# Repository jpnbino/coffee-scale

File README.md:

# Coffee Scale Controller

Open-hardware electronics for a coffee scale controller. The project contains
the KiCad design, revision history, manufacturing records, release tooling, and
a browser-based review portal.

**Review portal:** <https://jpnbino.github.io/coffee-scale/> — schematic, PCB,
3D model, Gerbers and build files from the latest `main` build. It shows a
prototype design for review, not a production or supplier approval.

*Revision E routed prototype, shown as a faithful KiCad-derived isometric render.
The image is for design review; the hardware is not yet production-approved.*

## Current status

- **Hardware:** Revision E routed prototype.
- **Firmware:** prototype MicroPython firmware, tested on a breadboard build, is in
  [coffee-scale-firmware](https://github.com/jpnbino/coffee-scale-firmware);
  it is not yet ported to this PCB.
- **Not complete:** Firmware for Rev E, physical validation, supplier approval, and final
  assembly decisions.
- **Authoritative design:** `src/`.
- **Historical records:** `src/fabrication/` and revision snapshots under `src/`.

This repository is public and intended for open-hardware development. A
maintainer still needs to choose and add the project's hardware, software, and
documentation licenses; no legal license was guessed.

## Repository map

| Path | Purpose |
| --- | --- |
| `src/` | KiCad sources, local libraries, models, revision snapshots, and historical fabrication data |
| `assembly/` | Assembly profile used by the release workflow |
| `scripts/legacy/` | Historical placement, routing, revision, and packaging utilities |
| `tools/` | Maintained release and portal build tooling |
| `docs/` | Detailed board, manufacturing, and compatibility documentation |
| `tests/` | Release and viewer regression checks |
| `web/` | Browser review portal source and pinned vendor assets |
| `build/`, `tmp/`, `work/`, `outputs/` | Generated or intermediate files; not committed |

## Quick start

Requirements (Windows, macOS or Linux):

- KiCad 10, which provides `kicad-cli`
- Node.js 22 or newer — no `npm install` needed; the tooling has no dependencies

From the repository root:

```sh
node release.mjs --validate-only   # ERC, DRC, schematic parity and dimensions
node release.mjs                   # full prototype release build
node preview.mjs                   # view it at http://127.0.0.1:8787 (see Review portal)
```

The same commands are available as `npm run validate`, `npm run release` and
`npm run preview`. `node release.mjs --require-assembly-ready` additionally
fails the build while assembly blockers remain.

`kicad-cli` is found from `--kicad-cli <path>`, then the `KICAD_CLI`
environment variable, then `PATH`, then the standard install location
(`C:/Program Files/KiCad/10.0/bin` on Windows,
`/Applications/KiCad/KiCad.app/Contents/MacOS` on macOS, `/usr/bin` on Linux).
Each build creates a new timestamped folder under `build/releases/`.

## Review portal

Every release build includes a browser-based review portal (`site/`):

| Page | What it shows |
| --- | --- |
| Overview | Board summary, status and key facts |
| Explore board | Top/bottom copper, schematic and 3D model with part search |
| Board statistics, Layer stackup | Counts and drill table; order parameters checked against KiCad, cross-section, track current estimates |
| Gerber inspection | The exact manufacturing files, with layer presets, measurement and checks before ordering (placement, paste, pin maps) |
| Build & manufacture, Enclosure & mechanics | Fabrication, assembly-draft and mechanical downloads |
| Versions & changes | Rev D, archived Rev E and the current build compared |
| Documentation | The notes in `docs/board/` |

### Online

<https://jpnbino.github.io/coffee-scale/> is republished automatically after
every push to `main`, once the tests and the full KiCad build have passed.
Pull requests are built and checked but never published.

### Locally

After a build, serve it with:

```sh
node release.mjs     # build first (a few minutes); needs KiCad
node preview.mjs     # then open http://127.0.0.1:8787
```

- `preview.mjs` serves the newest *complete* build in `build/releases/`.
  Stop it with Ctrl+C.
- Use `--port 8080` if 8787 is taken, or `--site <build>/site` to serve a
  specific build.
- The server only listens on your own machine (`127.0.0.1`); nothing is
  published.
- Don't open `index.html` by double-clicking it: browsers block the 3D model and
  interactive drawings on `file://` pages.
- After pulling changes to `web/` or `tools/`, run `node release.mjs` again.
  Existing builds keep the portal code they were built with.

### From a CI build

Each GitHub Actions run keeps its full build for 14 days. Open the run under
**Actions**, download **release-build** from *Artifacts*, unzip it, then:

```sh
node preview.mjs --site ~/Downloads/release-build/<build-id>/site
```

## Release contents

Each successful build contains:

- `source/` — isolated KiCad design snapshot
- `reports/` — ERC, DRC, netlist, statistics, and build log
- `fabrication/` — Gerbers, drills, and manufacturing notes
- `assembly/` — BOM, placement data, IPC-2581, stencil layers, and readiness
- `mechanical/` — STEP/DXF exports and interface data
- `site/` — review portal and downloadable packages
- `manifest.json` — hashes, tool versions, status, and readiness

The assembly profile in `assembly/profile.csv` is intentionally retained: the
release workflow reads it to apply population stages, sourcing metadata,
rotation corrections, and verification state. It is not proof of supplier
approval.

## Checks

```sh
npm test        # or: node --test tests/*.test.mjs
```

GitHub Actions runs these tests on Windows, macOS and Linux, then runs the
validation and a full release build inside the official, version-pinned
`kicad/kicad` container. The build is attached to each run as an artifact.

See `docs/board/` for the detailed circuit, assembly, mechanical and
manufacturing notes, and `docs/maintainer/` for how the portal's viewers work. Legacy utilities should be run from the repository root;
they write candidates and intermediate files to their existing revision and
`tmp/` locations.

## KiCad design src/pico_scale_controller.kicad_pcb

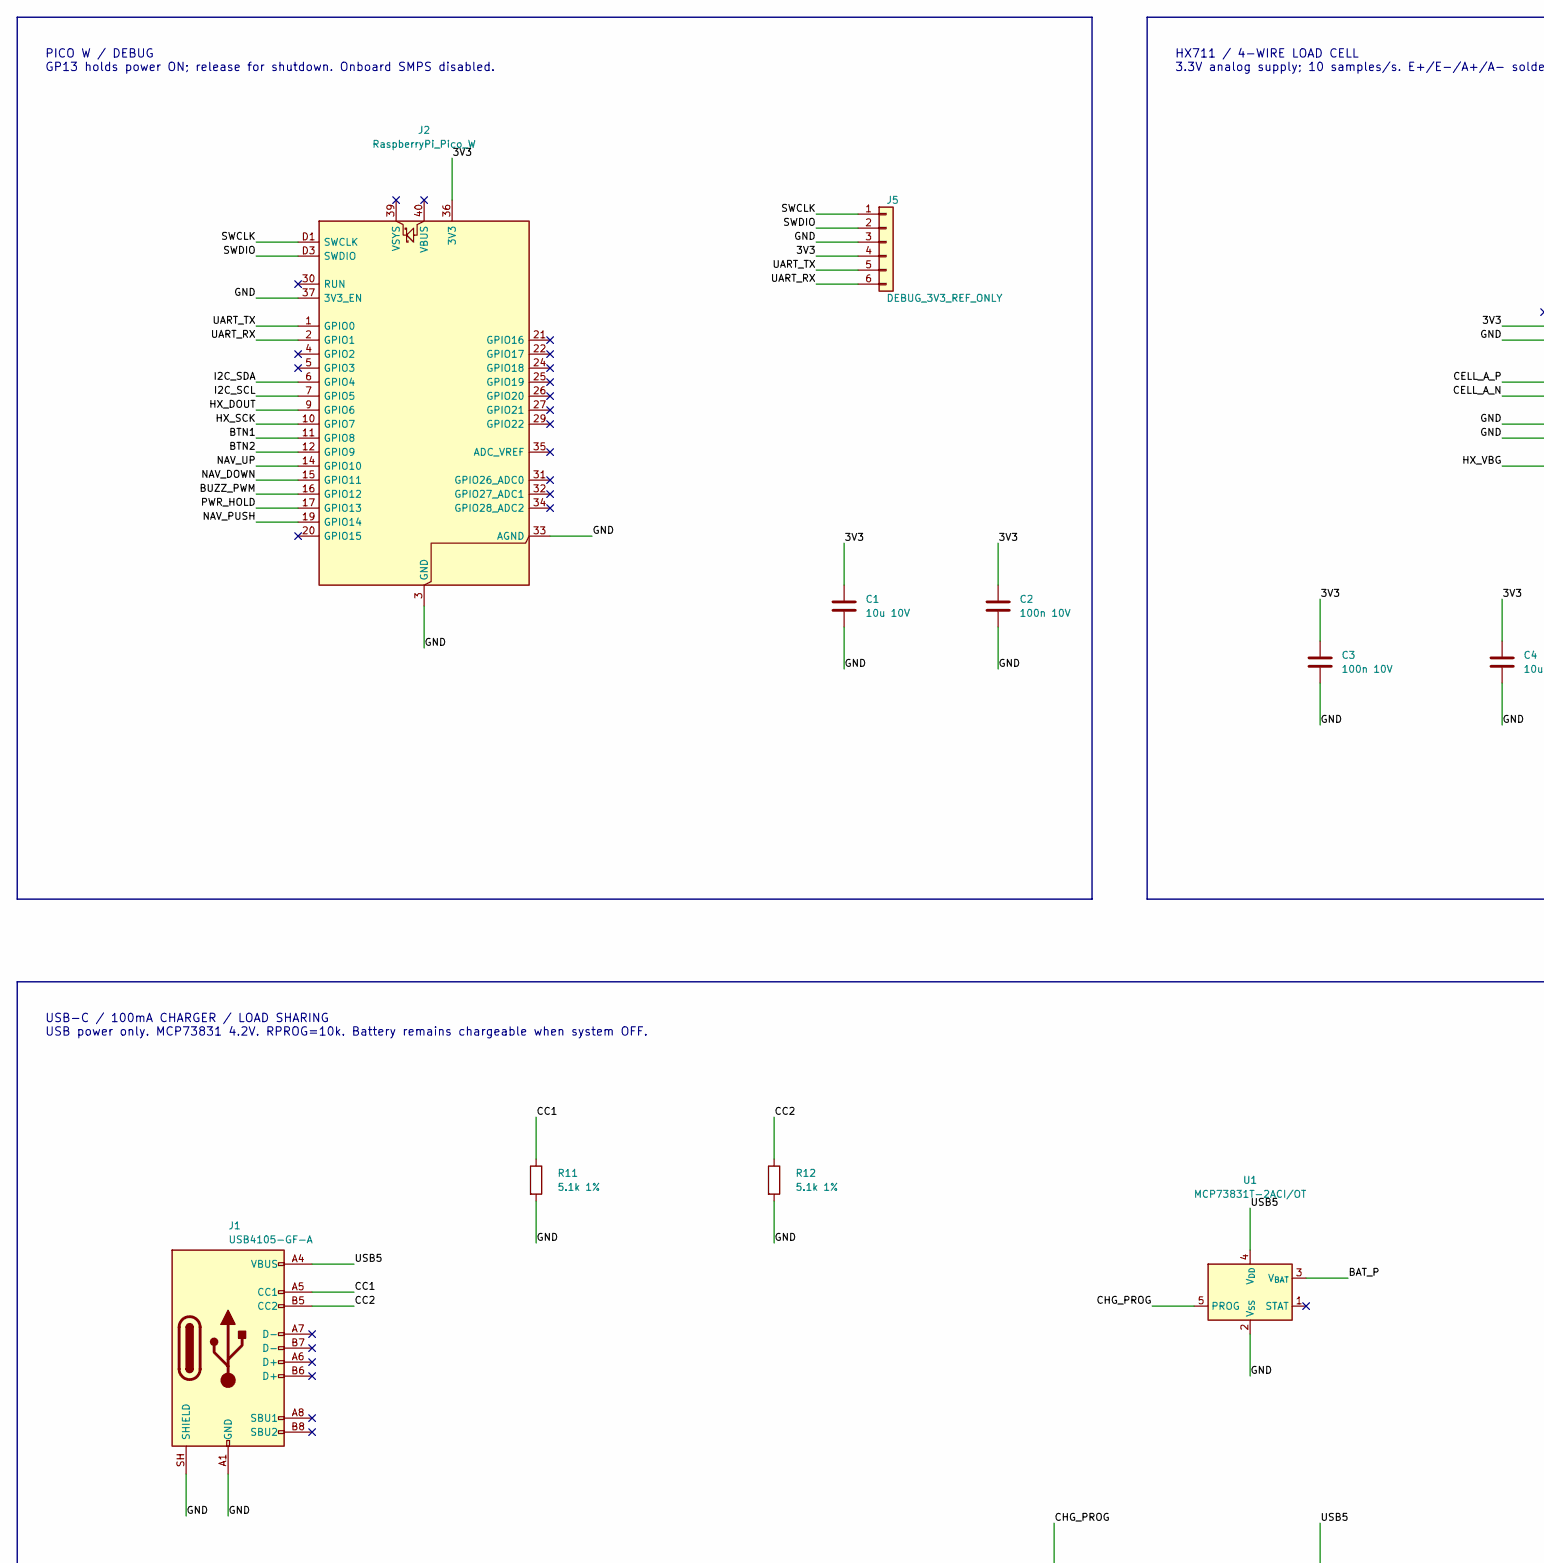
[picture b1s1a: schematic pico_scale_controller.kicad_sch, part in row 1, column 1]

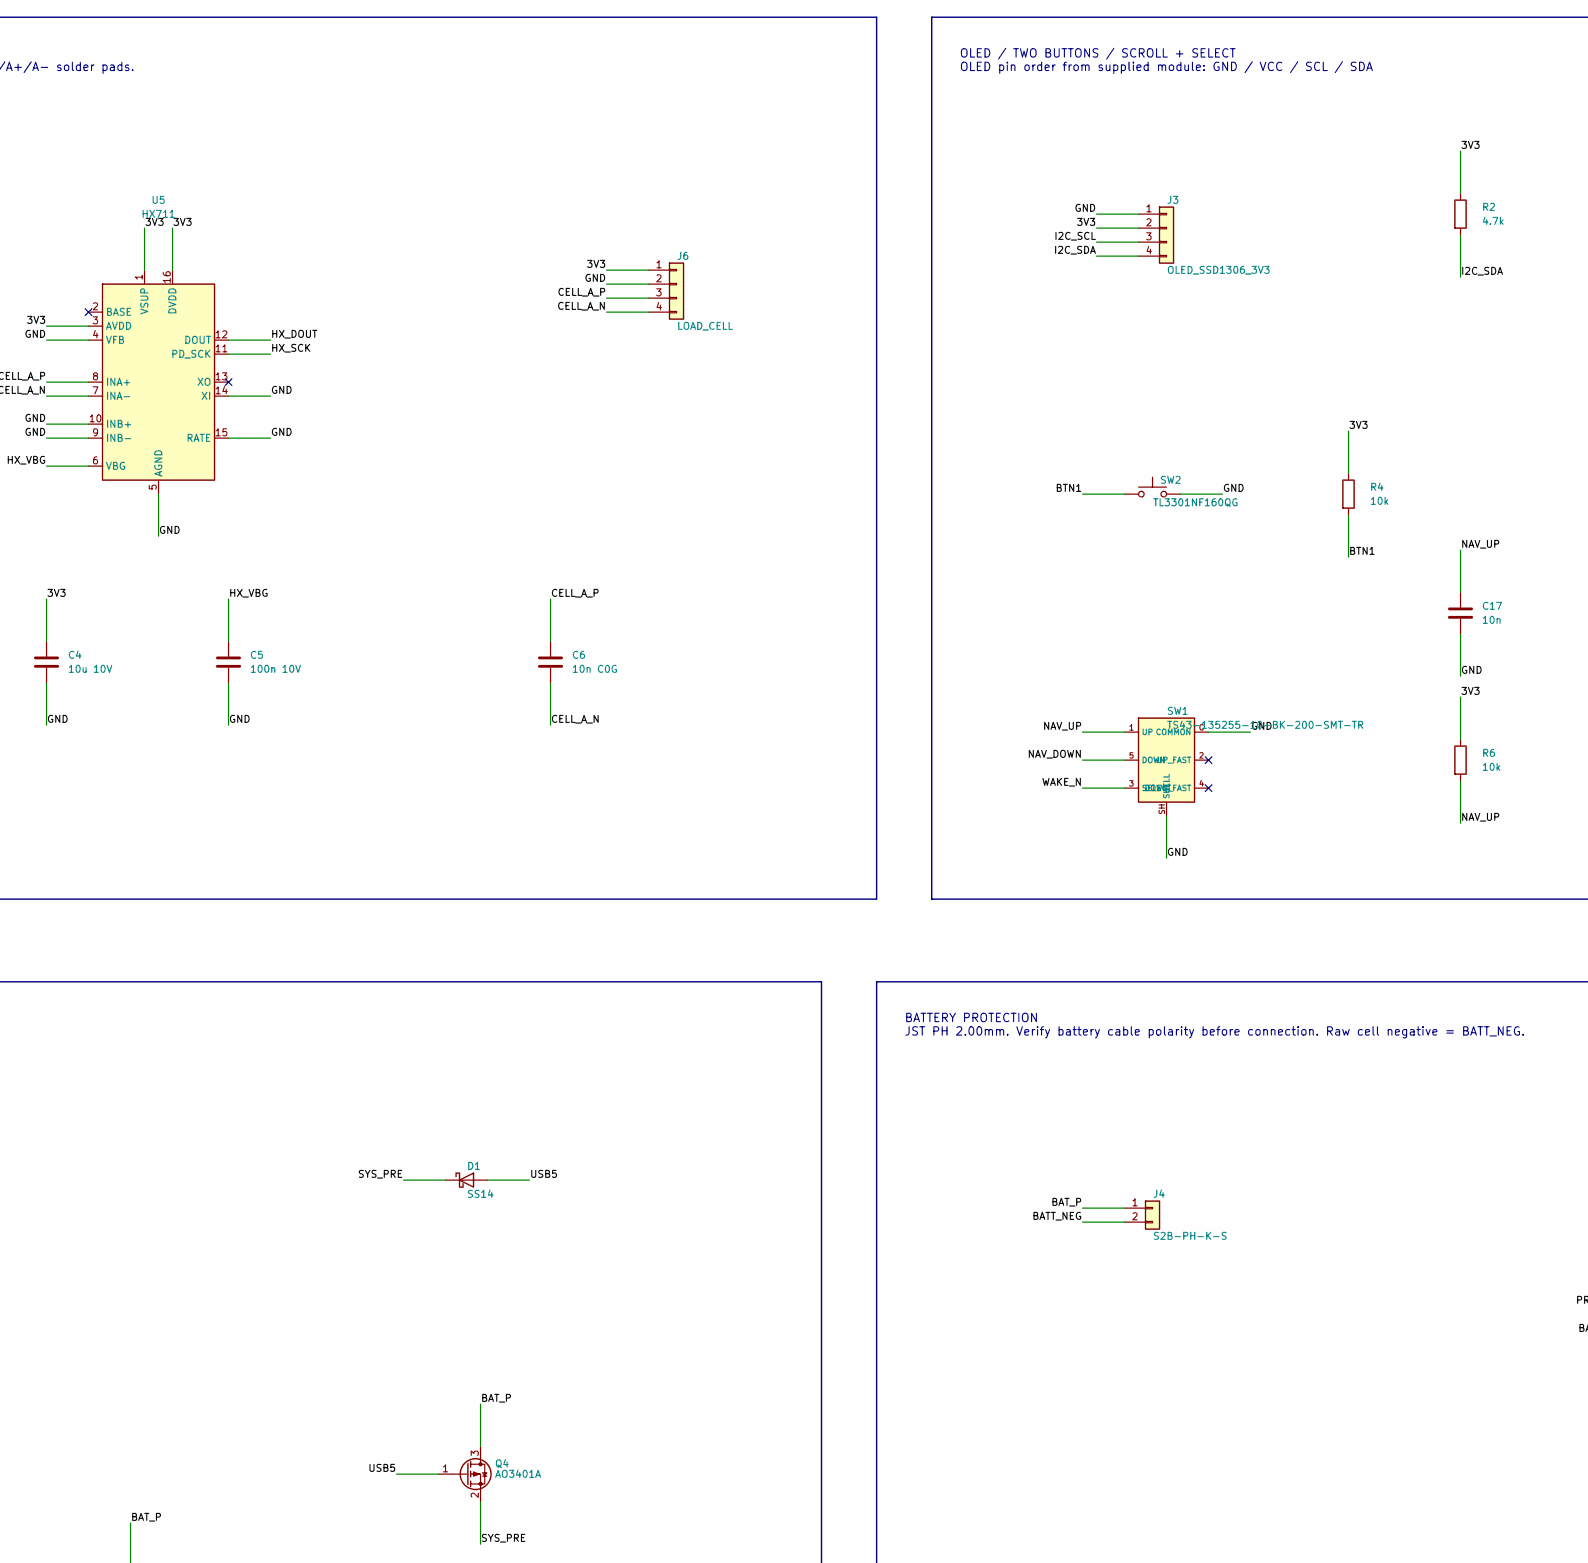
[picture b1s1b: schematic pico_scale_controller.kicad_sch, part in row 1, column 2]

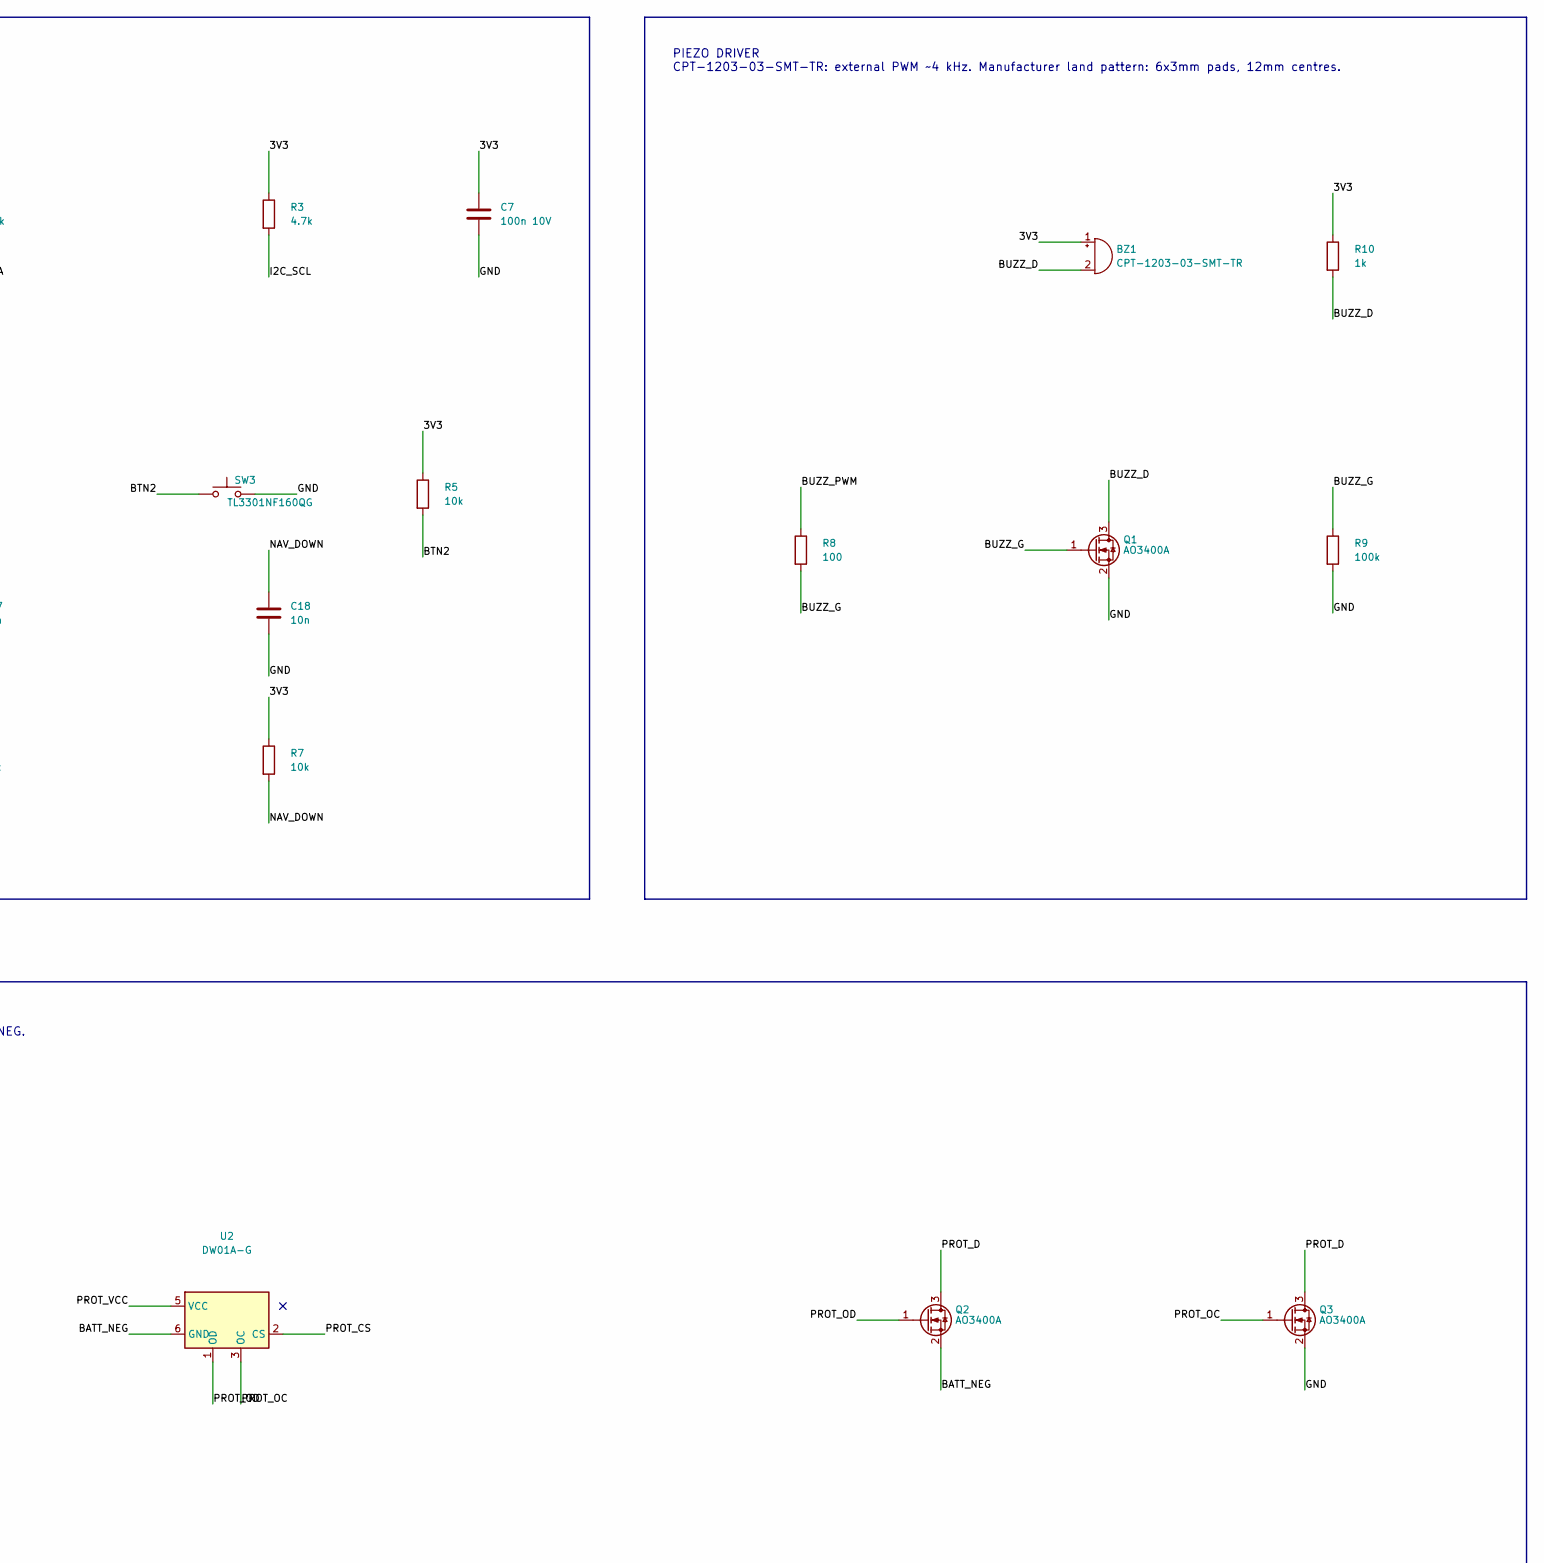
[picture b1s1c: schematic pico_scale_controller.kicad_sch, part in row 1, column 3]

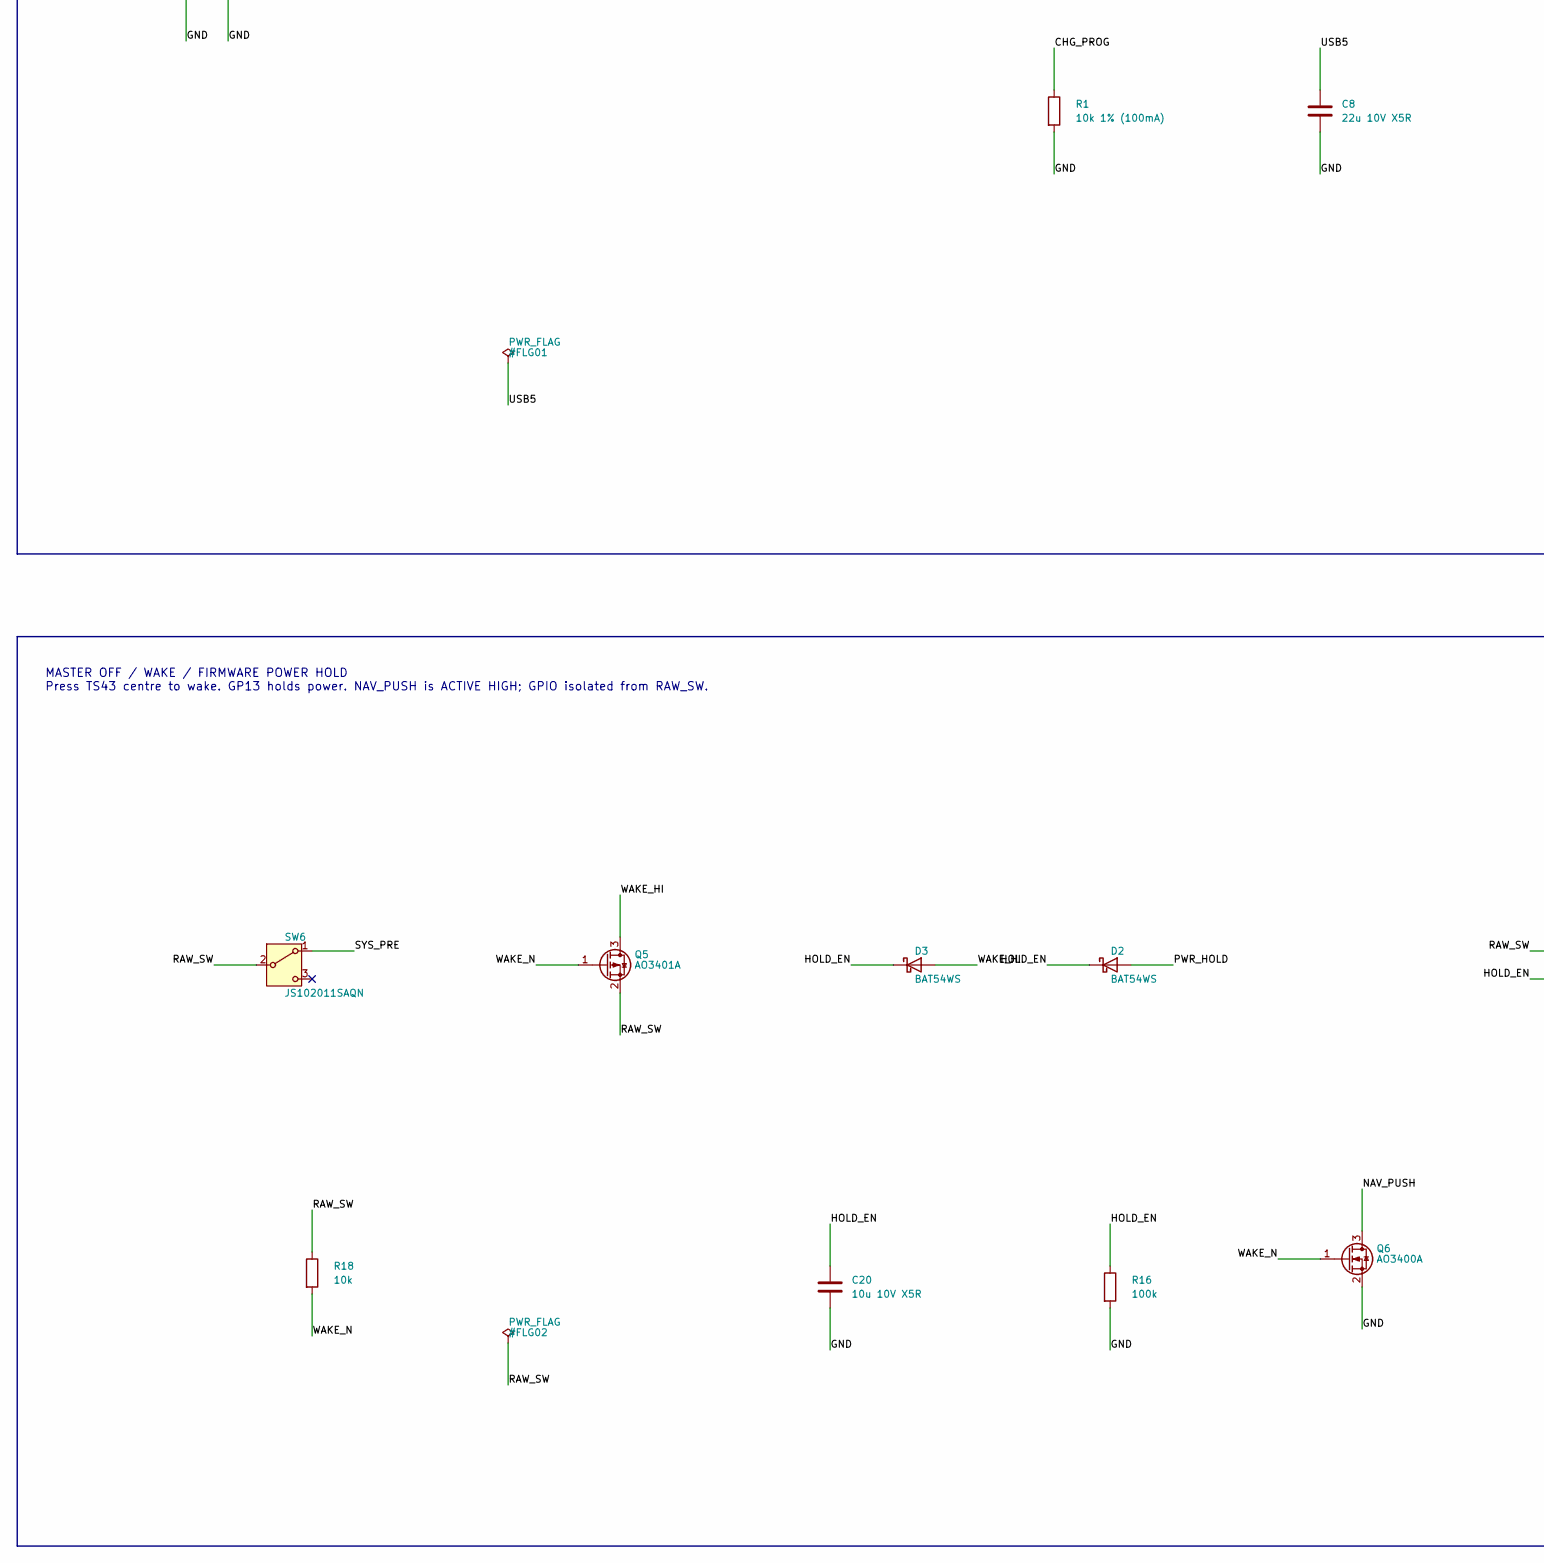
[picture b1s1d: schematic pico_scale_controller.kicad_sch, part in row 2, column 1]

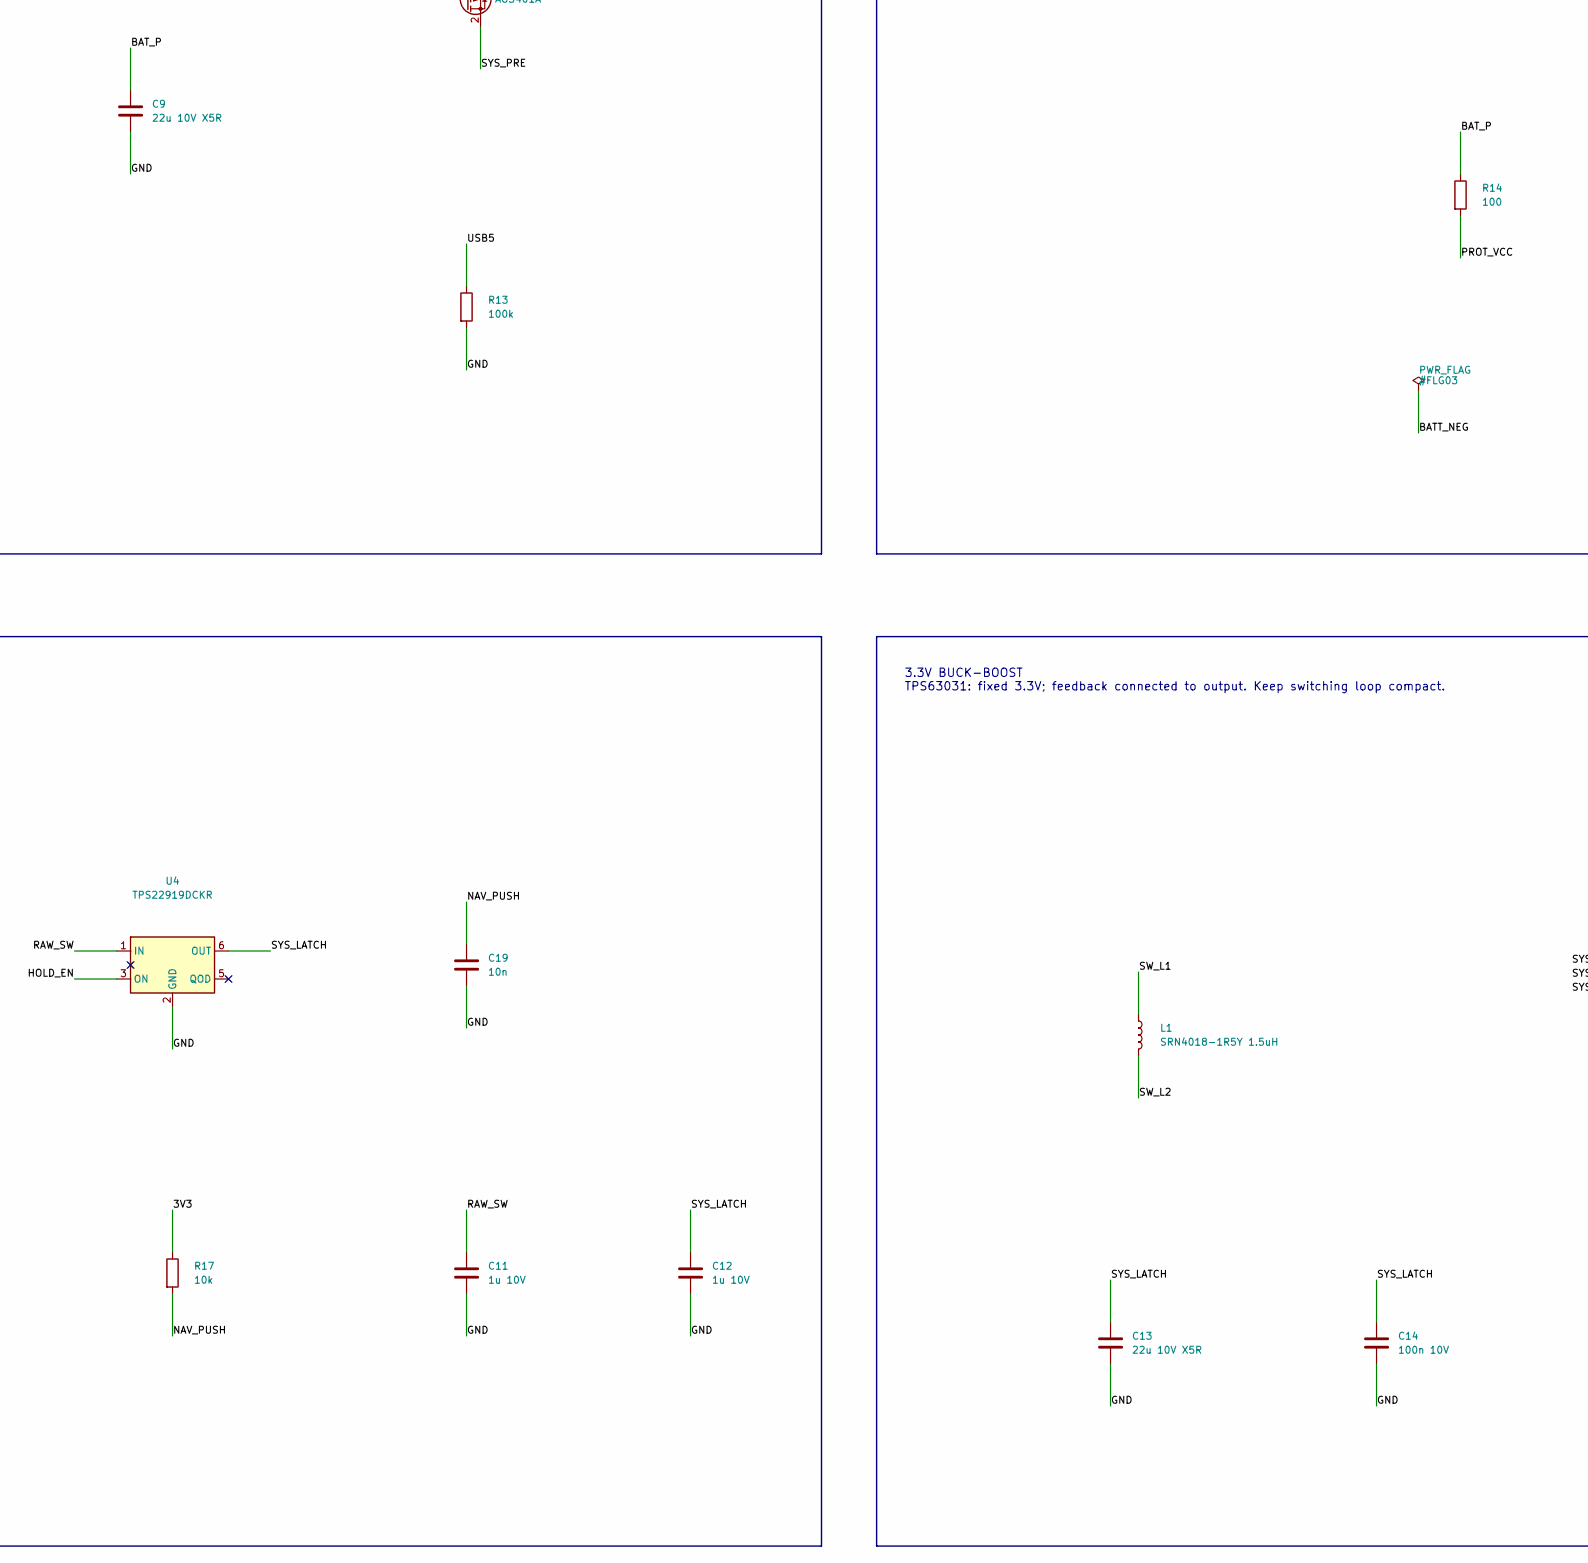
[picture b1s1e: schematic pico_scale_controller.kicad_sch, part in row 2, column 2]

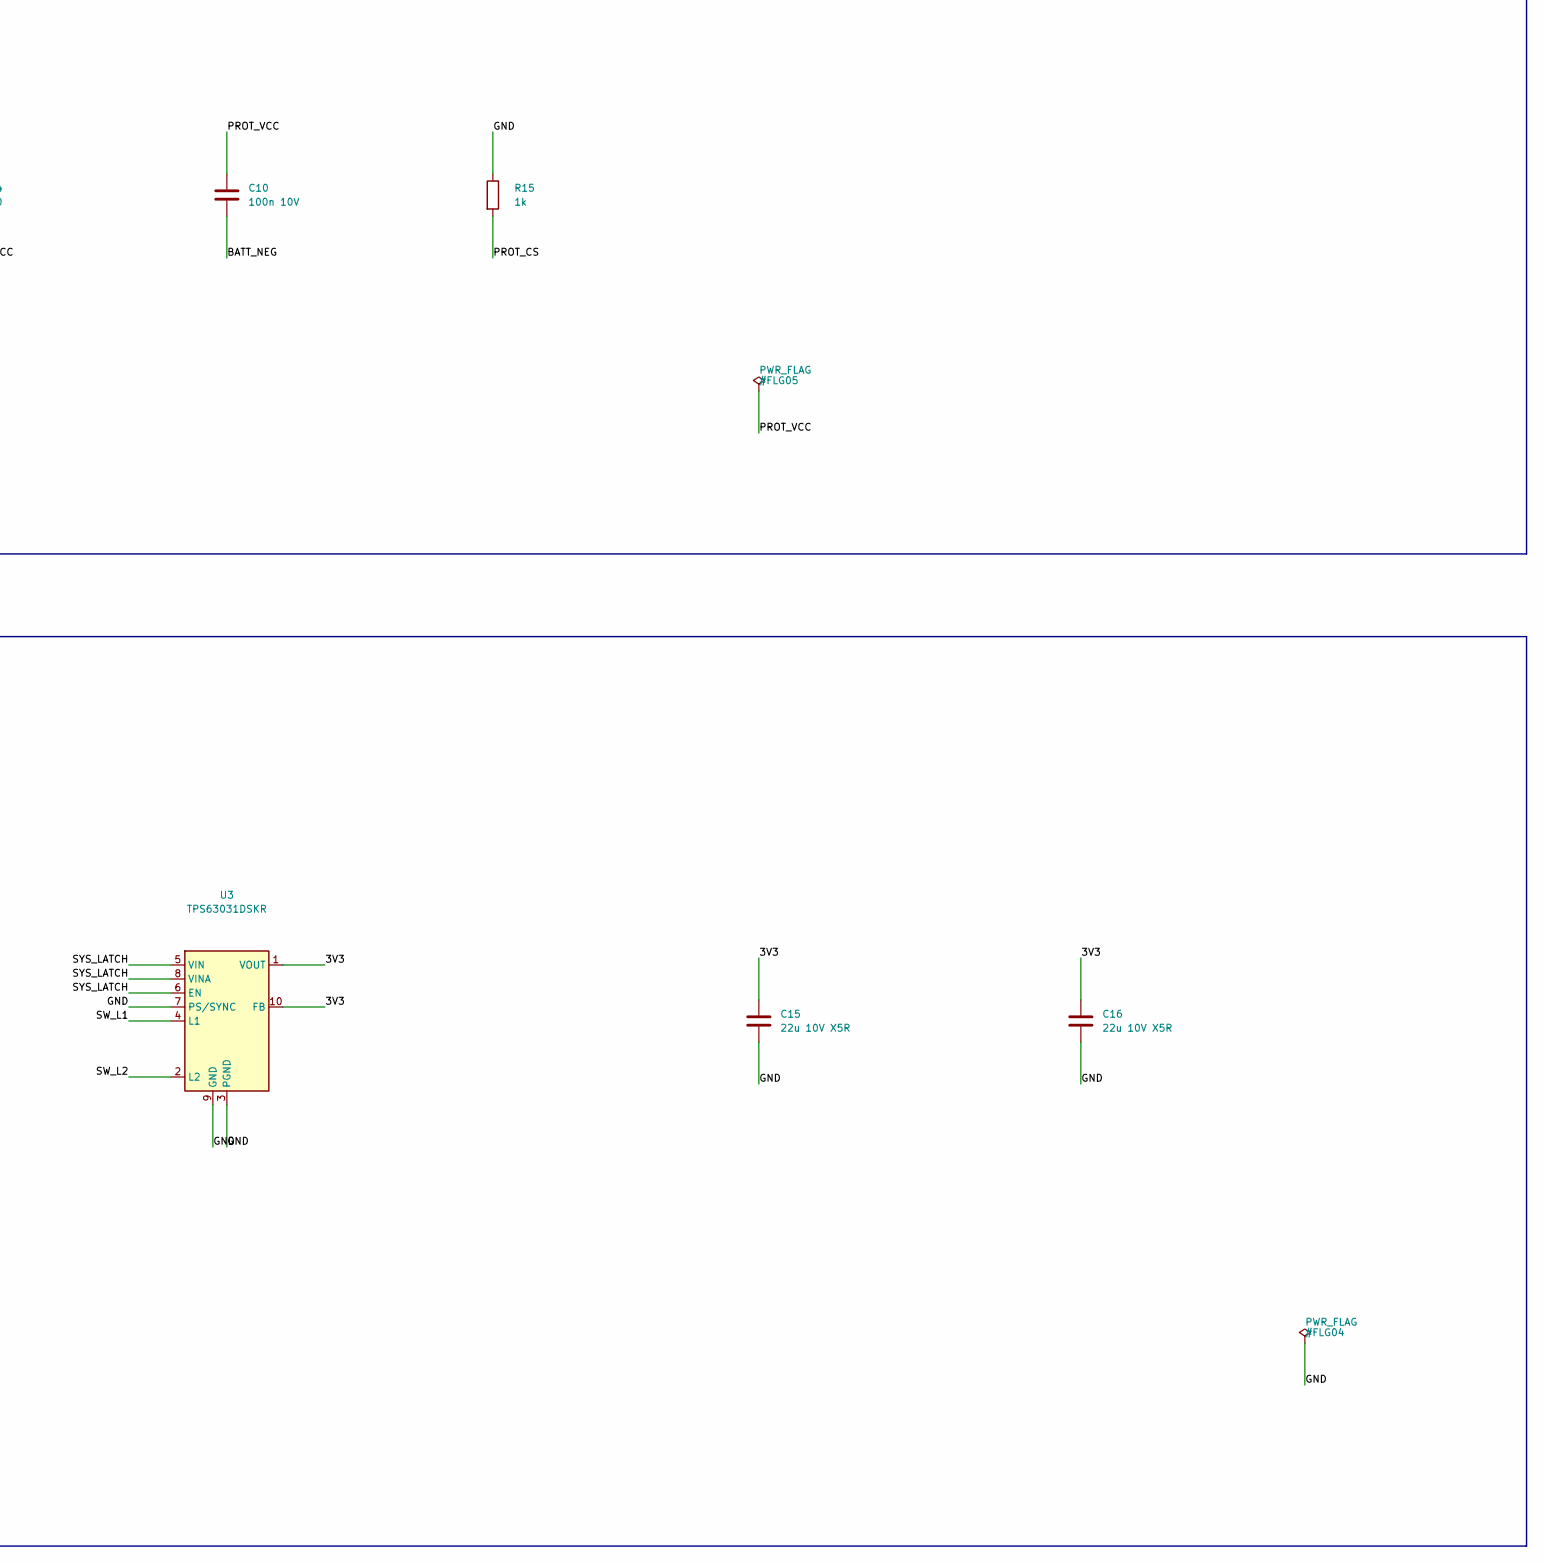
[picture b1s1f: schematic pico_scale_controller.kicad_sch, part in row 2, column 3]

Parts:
BZ1: CPT-1203-03-SMT-TR
C1, C4: 10u 10V; C_0603_1608Metric
C2, C3, C5, C7, C10, C14: 100n 10V; C_0603_1608Metric
C6: 10n C0G; C_0603_1608Metric
C8, C9, C13, C15, C16: 22u 10V X5R; C_0805_2012Metric
C11, C12: 1u 10V; C_0603_1608Metric
C17, C18, C19: 10n; C_0603_1608Metric
C20: 10u 10V X5R; C_0805_2012Metric
D1: SS14; D_SMA
D2, D3: BAT54WS; D_SOD-323
J1: USB4105-GF-A; USB4105_GND_Rounded
J2: RaspberryPi_Pico_W; Pico_W_Hybrid
J3: OLED_SSD1306_3V3; PinHeader_1x04_P2.54mm_Vertical
J4: S2B-PH-K-S; JST_PH_S2B-PH-K_1x02_P2.00mm_Horizontal
J5: DEBUG_3V3_REF_ONLY; PinHeader_1x06_P2.54mm_Vertical
J6: LOAD_CELL; LoadCell_4Pads
L1: SRN4018-1R5Y 1.5uH; L_Bourns-SRN4018
Q1, Q2, Q3, Q6: AO3400A; SOT-23
Q4, Q5: AO3401A; SOT-23
R1: 10k 1% (100mA); R_0603_1608Metric
R2, R3: 4.7k; R_0603_1608Metric
R4, R5, R6, R7, R17, R18: 10k; R_0603_1608Metric
R8, R14: 100; R_0603_1608Metric
R9, R13, R16: 100k; R_0603_1608Metric
R10, R15: 1k; R_0603_1608Metric
R11, R12: 5.1k 1%; R_0603_1608Metric
SW1: TS43-135255-10-BK-200-SMT-TR; TS43_135255
SW2, SW3: TL3301NF160QG; SW_Push_1P1T_NO_E-Switch_TL3301NxxxxxG
SW6: JS102011SAQN; SW_SPDT_CK_JS102011SAQN
U1: MCP73831T-2ACI/OT; SOT-23-5
U2: DW01A-G; SOT-23-6
U3: TPS63031DSKR; WSON-10-1EP_2.5x2.5mm_P0.5mm_EP1.2x2mm
U4: TPS22919DCKR; SOT-363_SC-70-6
U5: HX711; SOIC-16_3.9x9.9mm_P1.27mm

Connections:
/3V3: BZ1.1 (+), C1.1, C2.1, C3.1, C4.1, C7.1, C15.1, C16.1, J2.36 (3V3), J3.2, J5.4, J6.1, R2.1, R3.1, R4.1, R5.1, R6.1, R7.1, R10.1, R17.1, U3.1 (VOUT), U3.10 (FB), U5.1 (VSUP), U5.3 (AVDD), U5.16 (DVDD)
/BATT_NEG: C10.2, J4.2, Q2.2 (S), U2.6 (GND)
/BAT_P: C9.1, J4.1, Q4.3 (D), R14.1, U1.3 (V_{BAT})
/BTN1: J2.11 (GPIO8), R4.2, SW2.1
/BTN2: J2.12 (GPIO9), R5.2, SW3.1
/BUZZ_D: BZ1.2 (-), Q1.3 (D), R10.2
/BUZZ_G: Q1.1 (G), R8.2, R9.1
/BUZZ_PWM: J2.16 (GPIO12), R8.1
/CC1: J1.A5 (CC1), R11.1
/CC2: J1.B5 (CC2), R12.1
/CELL_A_N: C6.2, J6.4, U5.7 (INA-)
/CELL_A_P: C6.1, J6.3, U5.8 (INA+)
/CHG_PROG: R1.1, U1.5 (PROG)
/GND: C1.2, C2.2, C3.2, C4.2, C5.2, C7.2, C8.2, C9.2, C11.2, C12.2, C13.2, C14.2, C15.2, C16.2, C17.2, C18.2, C19.2, C20.2, J1.A1 (GND), J1.A12 (GND), J1.B1 (GND), J1.B12 (GND), J1.SH (SHIELD), J2.3 (GND), J2.8 (GND), J2.13 (GND), J2.18 (GND), J2.23 (GND), J2.28 (GND), J2.33 (AGND), J2.37 (3V3_EN), J2.38 (GND), J2.D2 (GND), J3.1, J5.3, J6.2, Q1.2 (S), Q3.2 (S), Q6.2 (S), R1.2, R9.2, R11.2, R12.2, R13.2, R15.1, R16.2, SW1.C (COMMON), SW1.SH (SHELL), SW2.2, SW3.2, U1.2 (V_{SS}), U3.3 (PGND), U3.7 (PS/SYNC), U3.9 (GND), U3.11 (PGND), U4.2 (GND), U5.4 (VFB), U5.5 (AGND), U5.9 (INB-), U5.10 (INB+), U5.14 (XI), U5.15 (RATE)
/HOLD_EN: C20.1, D2.1 (K), D3.1 (K), R16.1, U4.3 (ON)
/HX_DOUT: J2.9 (GPIO6), U5.12 (DOUT)
/HX_SCK: J2.10 (GPIO7), U5.11 (PD_SCK)
/HX_VBG: C5.1, U5.6 (VBG)
/I2C_SCL: J2.7 (GPIO5), J3.3, R3.2
/I2C_SDA: J2.6 (GPIO4), J3.4, R2.2
/NAV_DOWN: C18.1, J2.15 (GPIO11), R7.2, SW1.5 (DOWN)
/NAV_PUSH: C19.1, J2.19 (GPIO14), Q6.3 (D), R17.2
/NAV_UP: C17.1, J2.14 (GPIO10), R6.2, SW1.1 (UP)
/PROT_CS: R15.2, U2.2 (CS)
/PROT_D: Q2.3 (D), Q3.3 (D)
/PROT_OC: Q3.1 (G), U2.3 (OC)
/PROT_OD: Q2.1 (G), U2.1 (OD)
/PROT_VCC: C10.1, R14.2, U2.5 (VCC)
/PWR_HOLD: D2.2 (A), J2.17 (GPIO13)
/RAW_SW: C11.1, Q5.2 (S), R18.1, SW6.2 (B), U4.1 (IN)
/SWCLK: J2.D1 (SWCLK), J5.1
/SWDIO: J2.D3 (SWDIO), J5.2
/SW_L1: L1.1, U3.4 (L1)
/SW_L2: L1.2, U3.2 (L2)
/SYS_LATCH: C12.1, C13.1, C14.1, U3.5 (VIN), U3.6 (EN), U3.8 (VINA), U4.6 (OUT)
/SYS_PRE: D1.1 (K), Q4.2 (S), SW6.1 (A)
/UART_RX: J2.2 (GPIO1), J5.6
/UART_TX: J2.1 (GPIO0), J5.5
/USB5: C8.1, D1.2 (A), J1.A4 (VBUS), J1.A9 (VBUS), J1.B4 (VBUS), J1.B9 (VBUS), Q4.1 (G), R13.1, U1.4 (V_{DD})
/WAKE_HI: D3.2 (A), Q5.3 (D)
/WAKE_N: Q5.1 (G), Q6.1 (G), R18.2, SW1.3 (SELECT)

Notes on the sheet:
PICO W / DEBUG GP13 holds power ON; release for shutdown. Onboard SMPS disabled.
HX711 / 4-WIRE LOAD CELL 3.3V analog supply; 10 samples/s. E+/E-/A+/A- solder pads.
OLED / TWO BUTTONS / SCROLL + SELECT OLED pin order from supplied module: GND / VCC / SCL / SDA
PIEZO DRIVER CPT-1203-03-SMT-TR: external PWM ~4 kHz. Manufacturer land pattern: 6x3mm pads, 12mm centres.
USB-C / 100mA CHARGER / LOAD SHARING USB power only. MCP73831 4.2V. RPROG=10k. Battery remains chargeable when system OFF.
BATTERY PROTECTION JST PH 2.00mm. Verify battery cable polarity before connection. Raw cell negative = BATT_NEG.
MASTER OFF / WAKE / FIRMWARE POWER HOLD Press TS43 centre to wake. GP13 holds power. NAV_PUSH is ACTIVE HIGH; GPIO isolated from RAW_SW.
3.3V BUCK-BOOST TPS63031: fixed 3.3V; feedback connected to output. Keep switching loop compact.

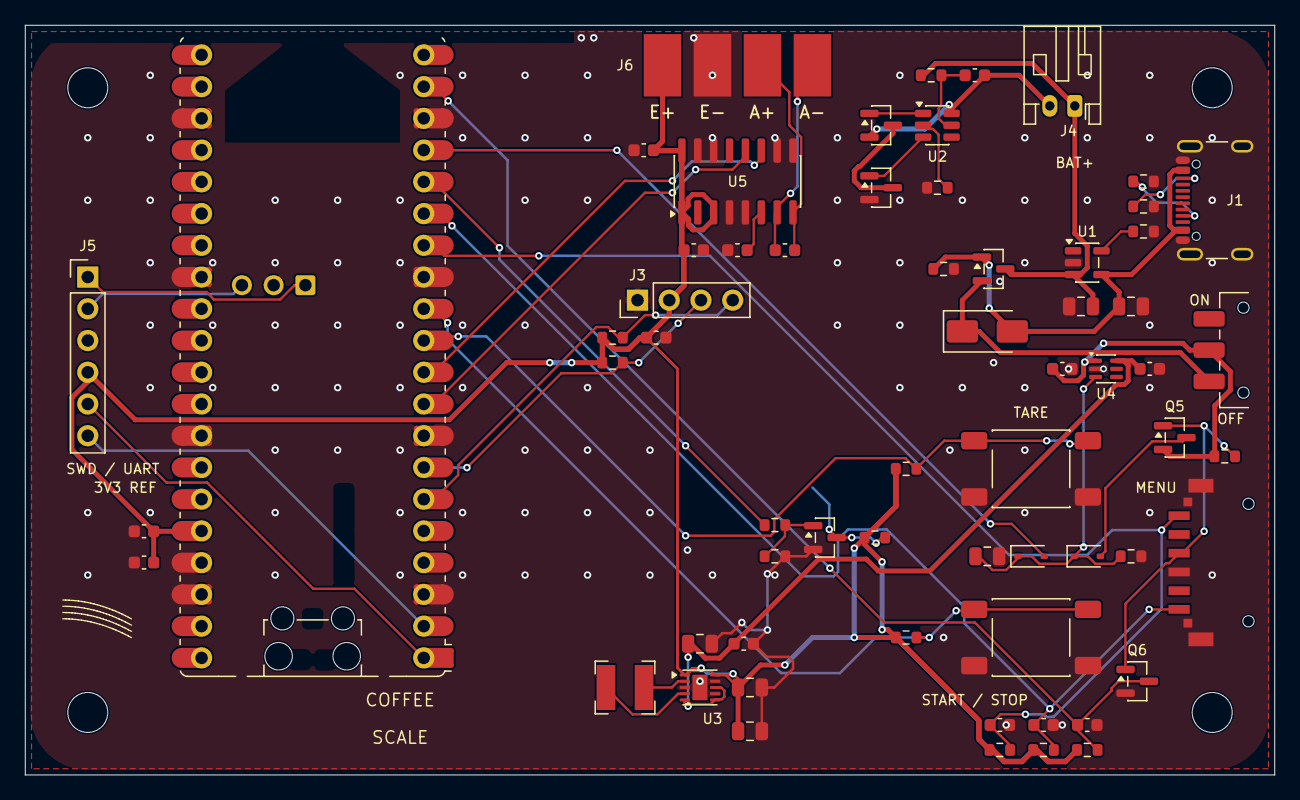
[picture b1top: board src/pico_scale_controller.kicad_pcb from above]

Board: 2 copper layers, 100.0 x 60.0 mm, 68 parts (1 on the bottom side), 41 nets.

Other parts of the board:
H1, H2, H3, H4: MountingHole_3.2mm_M3

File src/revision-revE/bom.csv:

Reference,Value / part,Footprint,Side
BZ1,CPT-1203-03-SMT-TR,CPT-1203-03-SMT-TR,bottom
C1,10u 10V,C_0603_1608Metric,top
C10,100n 10V,C_0603_1608Metric,top
C11,1u 10V,C_0603_1608Metric,top
C12,1u 10V,C_0603_1608Metric,top
C13,22u 10V X5R,C_0805_2012Metric,top
C14,100n 10V,C_0603_1608Metric,top
C15,22u 10V X5R,C_0805_2012Metric,top
C16,22u 10V X5R,C_0805_2012Metric,top
C17,10n,C_0603_1608Metric,top
C18,10n,C_0603_1608Metric,top
C19,10n,C_0603_1608Metric,top
C2,100n 10V,C_0603_1608Metric,top
C20,10u 10V X5R,C_0805_2012Metric,top
C3,100n 10V,C_0603_1608Metric,top
C4,10u 10V,C_0603_1608Metric,top
C5,100n 10V,C_0603_1608Metric,top
C6,10n C0G,C_0603_1608Metric,top
C7,100n 10V,C_0603_1608Metric,top
C8,22u 10V X5R,C_0805_2012Metric,top
C9,22u 10V X5R,C_0805_2012Metric,top
D1,SS14,D_SMA,top
D2,BAT54WS,D_SOD-323,top
D3,BAT54WS,D_SOD-323,top
H1,MountingHole_3.2mm_M3,MountingHole_3.2mm_M3,top
H2,MountingHole_3.2mm_M3,MountingHole_3.2mm_M3,top
H3,MountingHole_3.2mm_M3,MountingHole_3.2mm_M3,top
H4,MountingHole_3.2mm_M3,MountingHole_3.2mm_M3,top
J1,USB4105-GF-A,USB4105_GND_Rounded,top
J2,RaspberryPi_Pico_W,Pico_W_Hybrid,top
J3,OLED_SSD1306_3V3,PinHeader_1x04_P2.54mm_Vertical,top
J4,S2B-PH-K-S,JST_PH_S2B-PH-K_1x02_P2.00mm_Horizontal,top
J5,DEBUG_3V3_REF_ONLY,PinHeader_1x06_P2.54mm_Vertical,top
J6,LOAD_CELL,LoadCell_4Pads,top
L1,SRN4018-1R5Y 1.5uH,L_Bourns-SRN4018,top
Q1,AO3400A,SOT-23,top
Q2,AO3400A,SOT-23,top
Q3,AO3400A,SOT-23,top
Q4,AO3401A,SOT-23,top
Q5,AO3401A,SOT-23,top
Q6,AO3400A,SOT-23,top
R1,10k 1% (100mA),R_0603_1608Metric,top
R10,1k,R_0603_1608Metric,top
R11,5.1k 1%,R_0603_1608Metric,top
R12,5.1k 1%,R_0603_1608Metric,top
R13,100k,R_0603_1608Metric,top
R14,100,R_0603_1608Metric,top
R15,1k,R_0603_1608Metric,top
R16,100k,R_0603_1608Metric,top
R17,10k,R_0603_1608Metric,top
R18,10k,R_0603_1608Metric,top
R2,4.7k,R_0603_1608Metric,top
R3,4.7k,R_0603_1608Metric,top
R4,10k,R_0603_1608Metric,top
R5,10k,R_0603_1608Metric,top
R6,10k,R_0603_1608Metric,top
R7,10k,R_0603_1608Metric,top
R8,100,R_0603_1608Metric,top
R9,100k,R_0603_1608Metric,top
SW1,TS43-135255-10-BK-200-SMT-TR,TS43_135255,top
SW2,TL3301NF160QG,SW_Push_1P1T_NO_E-Switch_TL3301NxxxxxG,top
SW3,TL3301NF160QG,SW_Push_1P1T_NO_E-Switch_TL3301NxxxxxG,top
SW6,JS102011SAQN,SW_SPDT_CK_JS102011SAQN,top
U1,MCP73831T-2ACI/OT,SOT-23-5,top
U2,DW01A-G,SOT-23-6,top
U3,TPS63031DSKR,WSON-10-1EP_2.5x2.5mm_P0.5mm_EP1.2x2mm,top
U4,TPS22919DCKR,SOT-363_SC-70-6,top
U5,HX711,SOIC-16_3.9x9.9mm_P1.27mm,top
